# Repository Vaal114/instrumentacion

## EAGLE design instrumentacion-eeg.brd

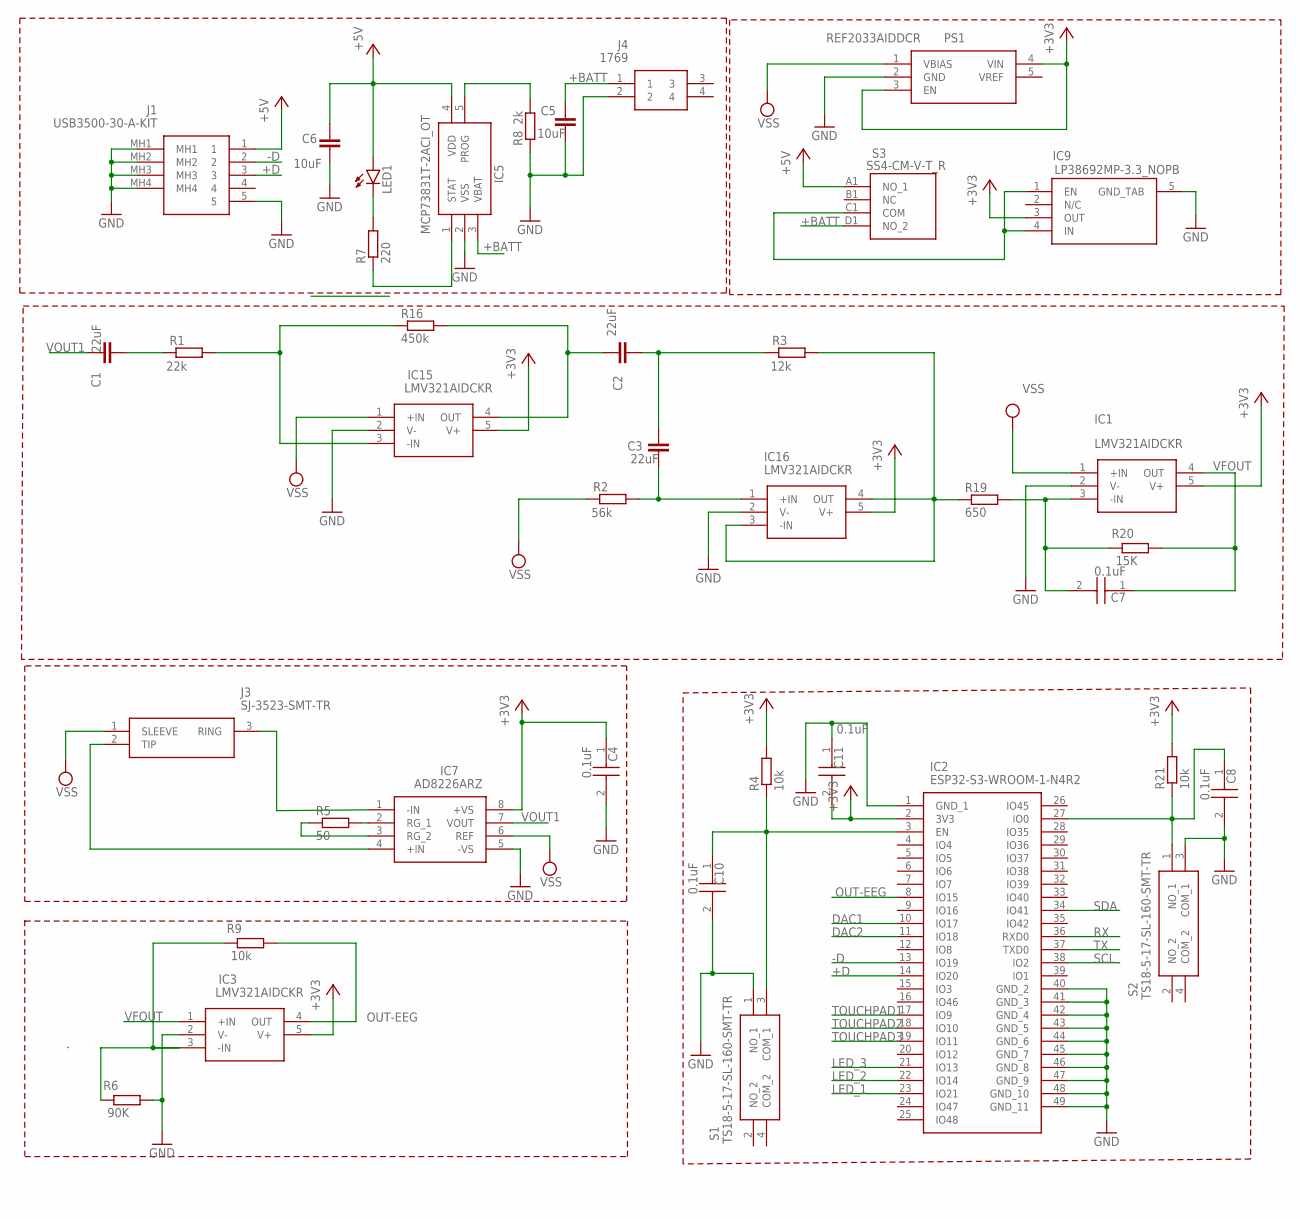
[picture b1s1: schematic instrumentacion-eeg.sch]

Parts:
C1, C2, C3, C5, C6: C-EUC0805; C0805
C4, C7, C8, C10, C11: 0.1uF; CAPC2012X140N
IC1, IC3, IC15, IC16: LMV321AIDCKR; SOT65P210X110-5N
IC2: ESP32-S3-WROOM-1-N4R2; ESP32S3WROOM1N4R2
IC5: MCP73831T-2ACI_OT; SOT95P270X145-5N
IC7: AD8226ARZ; SOIC127P600X175-8N
IC9: LP38692MP-3.3_NOPB; SOT150P700X180-5N
J1: USB3500-30-A-KIT; USB350030AKIT
J3: SJ-3523-SMT-TR; SJ3523SMTTR
J4: 1769
LED1: LEDCHIP-LED0805; CHIP-LED0805
PS1: REF2033AIDDCR; SOT95P280X110-5N
R1, R2, R3: R-EU_R0805; R0805
R4, R9, R21: 10k; R0805
R5: 50; R0805
R6: 90K; R0805
R7: 220; R0805
R8: 2k; R0805
R16: 450k; R0805
R19: 650; R0805
R20: 15K; R0805
S1, S2: TS18-5-17-SL-160-SMT-TR; TS18517SL160SMTTR
S3: SS4-CM-V-T_R; SS4CMVTR

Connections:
+3V3: C4.1, C11.2, IC1.5 (V+), IC2.2 (3V3), IC3.5 (V+), IC7.8 (+VS), IC9.3 (OUT), IC15.5 (V+), IC16.5 (V+), PS1.3 (EN), PS1.4 (VIN), R4.2, R21.2
+5V: C6.2, IC5.4 (VDD), J1.1, LED1.A, S3.A1 (NO_1)
+BATT: C5.2, IC5.3 (VBAT), J4.1, S3.D1 (NO_2)
+D: IC2.14 (IO20), J1.3
-D: IC2.13 (IO19), J1.2
DAC1: IC2.10 (IO17)
DAC2: IC2.11 (IO18)
GND: C4.2, C5.1, C6.1, C8.2, C10.2, C11.1, IC1.2 (V-), IC2.1 (GND_1), IC2.40 (GND_2), IC2.41 (GND_3), IC2.42 (GND_4), IC2.43 (GND_5), IC2.44 (GND_6), IC2.45 (GND_7), IC2.46 (GND_8), IC2.47 (GND_9), IC2.48 (GND_10), IC2.49 (GND_11), IC3.2 (V-), IC5.2 (VSS), IC7.5 (-VS), IC9.5 (GND_TAB), IC15.2 (V-), IC16.2 (V-), J1.5, J1.MH1, J1.MH2, J1.MH3, J1.MH4, J4.2, PS1.2 (GND), R6.2, R8.1, S1.1 (NO_1), S2.3 (COM_1)
LED_1: IC2.23 (IO21)
LED_2: IC2.22 (IO14)
LED_3: IC2.21 (IO13)
unnamed: IC7.4 (+IN), J3.2 (TIP)
unnamed: C1.2, R1.1
unnamed: C3.1, IC16.1 (+IN), R2.2
unnamed: C2.2, C3.2, R3.1
unnamed: C10.1, IC2.3 (EN), R4.1, S1.3 (COM_1)
unnamed: IC16.3 (-IN), IC16.4 (OUT), R3.2, R19.1
unnamed: C7.2, IC1.3 (-IN), R19.2, R20.1
unnamed: IC7.2 (RG_1), R5.2
unnamed: IC7.1 (-IN), J3.3 (RING)
unnamed: IC7.3 (RG_2), R5.1
unnamed: C8.1, IC2.27 (IO0), R21.1, S2.1 (NO_1)
unnamed: IC3.3 (-IN), R6.1, R9.1
unnamed: IC5.5 (PROG), R8.2
unnamed: IC5.1 (STAT), R7.1
unnamed: LED1.C, R7.2
unnamed: IC9.1 (EN), IC9.4 (IN), S3.C1 (COM)
unnamed: IC15.3 (-IN), R1.2, R16.1
unnamed: C2.1, IC15.4 (OUT), R16.2
OUT-EEG: IC2.8 (IO15), IC3.4 (OUT), R9.2
RX: IC2.36 (RXD0)
SCL: IC2.38 (IO2)
SDA: IC2.34 (IO41)
TOUCHPAD1: IC2.17 (IO9)
TOUCHPAD2: IC2.18 (IO10)
TOUCHPAD3: IC2.19 (IO11)
TX: IC2.37 (TXD0)
VFOUT: C7.1, IC1.4 (OUT), IC3.1 (+IN), R20.2
VOUT1: C1.1, IC7.7 (VOUT)
VSS: IC1.1 (+IN), IC7.6 (REF), IC15.1 (+IN), J3.1 (SLEEVE), PS1.1 (VBIAS), R2.1

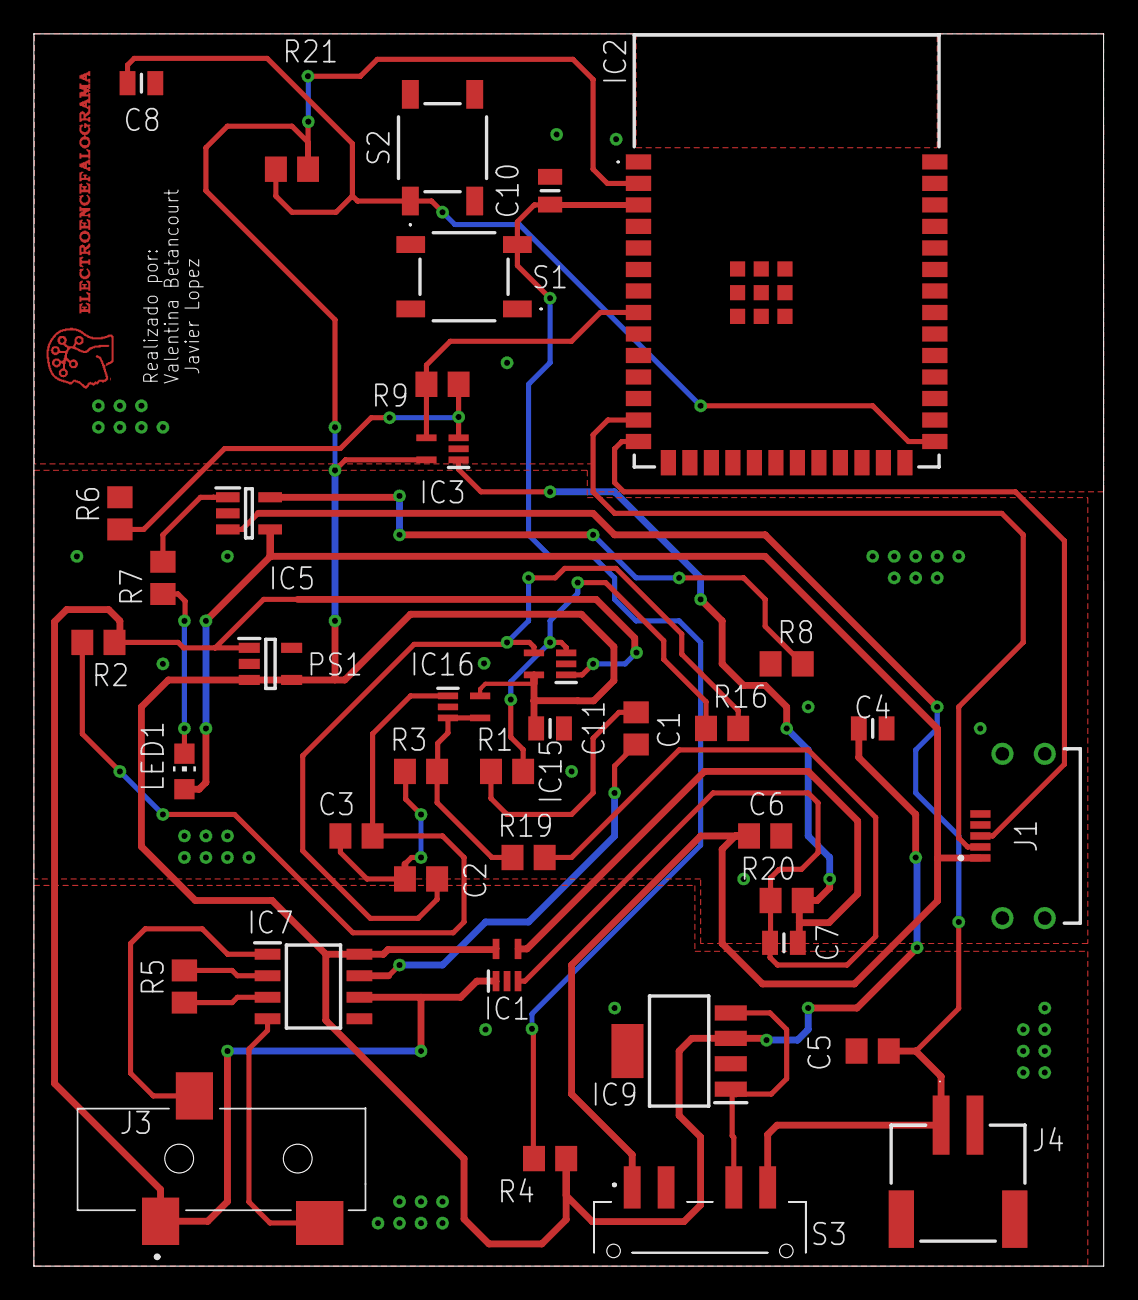
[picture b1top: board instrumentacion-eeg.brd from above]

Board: 2 copper layers, 63.2 x 72.8 mm, 39 parts (0 on the bottom side), 28 nets.

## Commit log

2025-10-10 hoja de datos para prueba
2025-10-10 Eliminado archivo innecesario
2025-10-10 agrego archivo esquematico
2025-10-10 Se corrigieron algunos bloques y se anoto lo faltante
2025-10-31 se agrego el pcb
2025-10-31 se corrigio el amplificador final
2025-11-03 Agrego correccion de amplificador
2025-11-07 Agrego avance de PCB
2025-11-07 Agrego PCB para ultima revision
2025-11-07 Agrego PCB para revisiones
2025-11-07 Agrego archivos
2025-11-07 fix: algunos errores corregidos en el PCB
2025-11-24 Agrego archivos finales
2025-11-24 Agrego informe
